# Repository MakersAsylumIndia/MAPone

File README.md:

MAPone
======

a really bare bones Arduino using ATMega 328P DIP, SPI and Serial Interfaces and a few LEDs. Arduino stripped down to bare basics so everyone can afford it.

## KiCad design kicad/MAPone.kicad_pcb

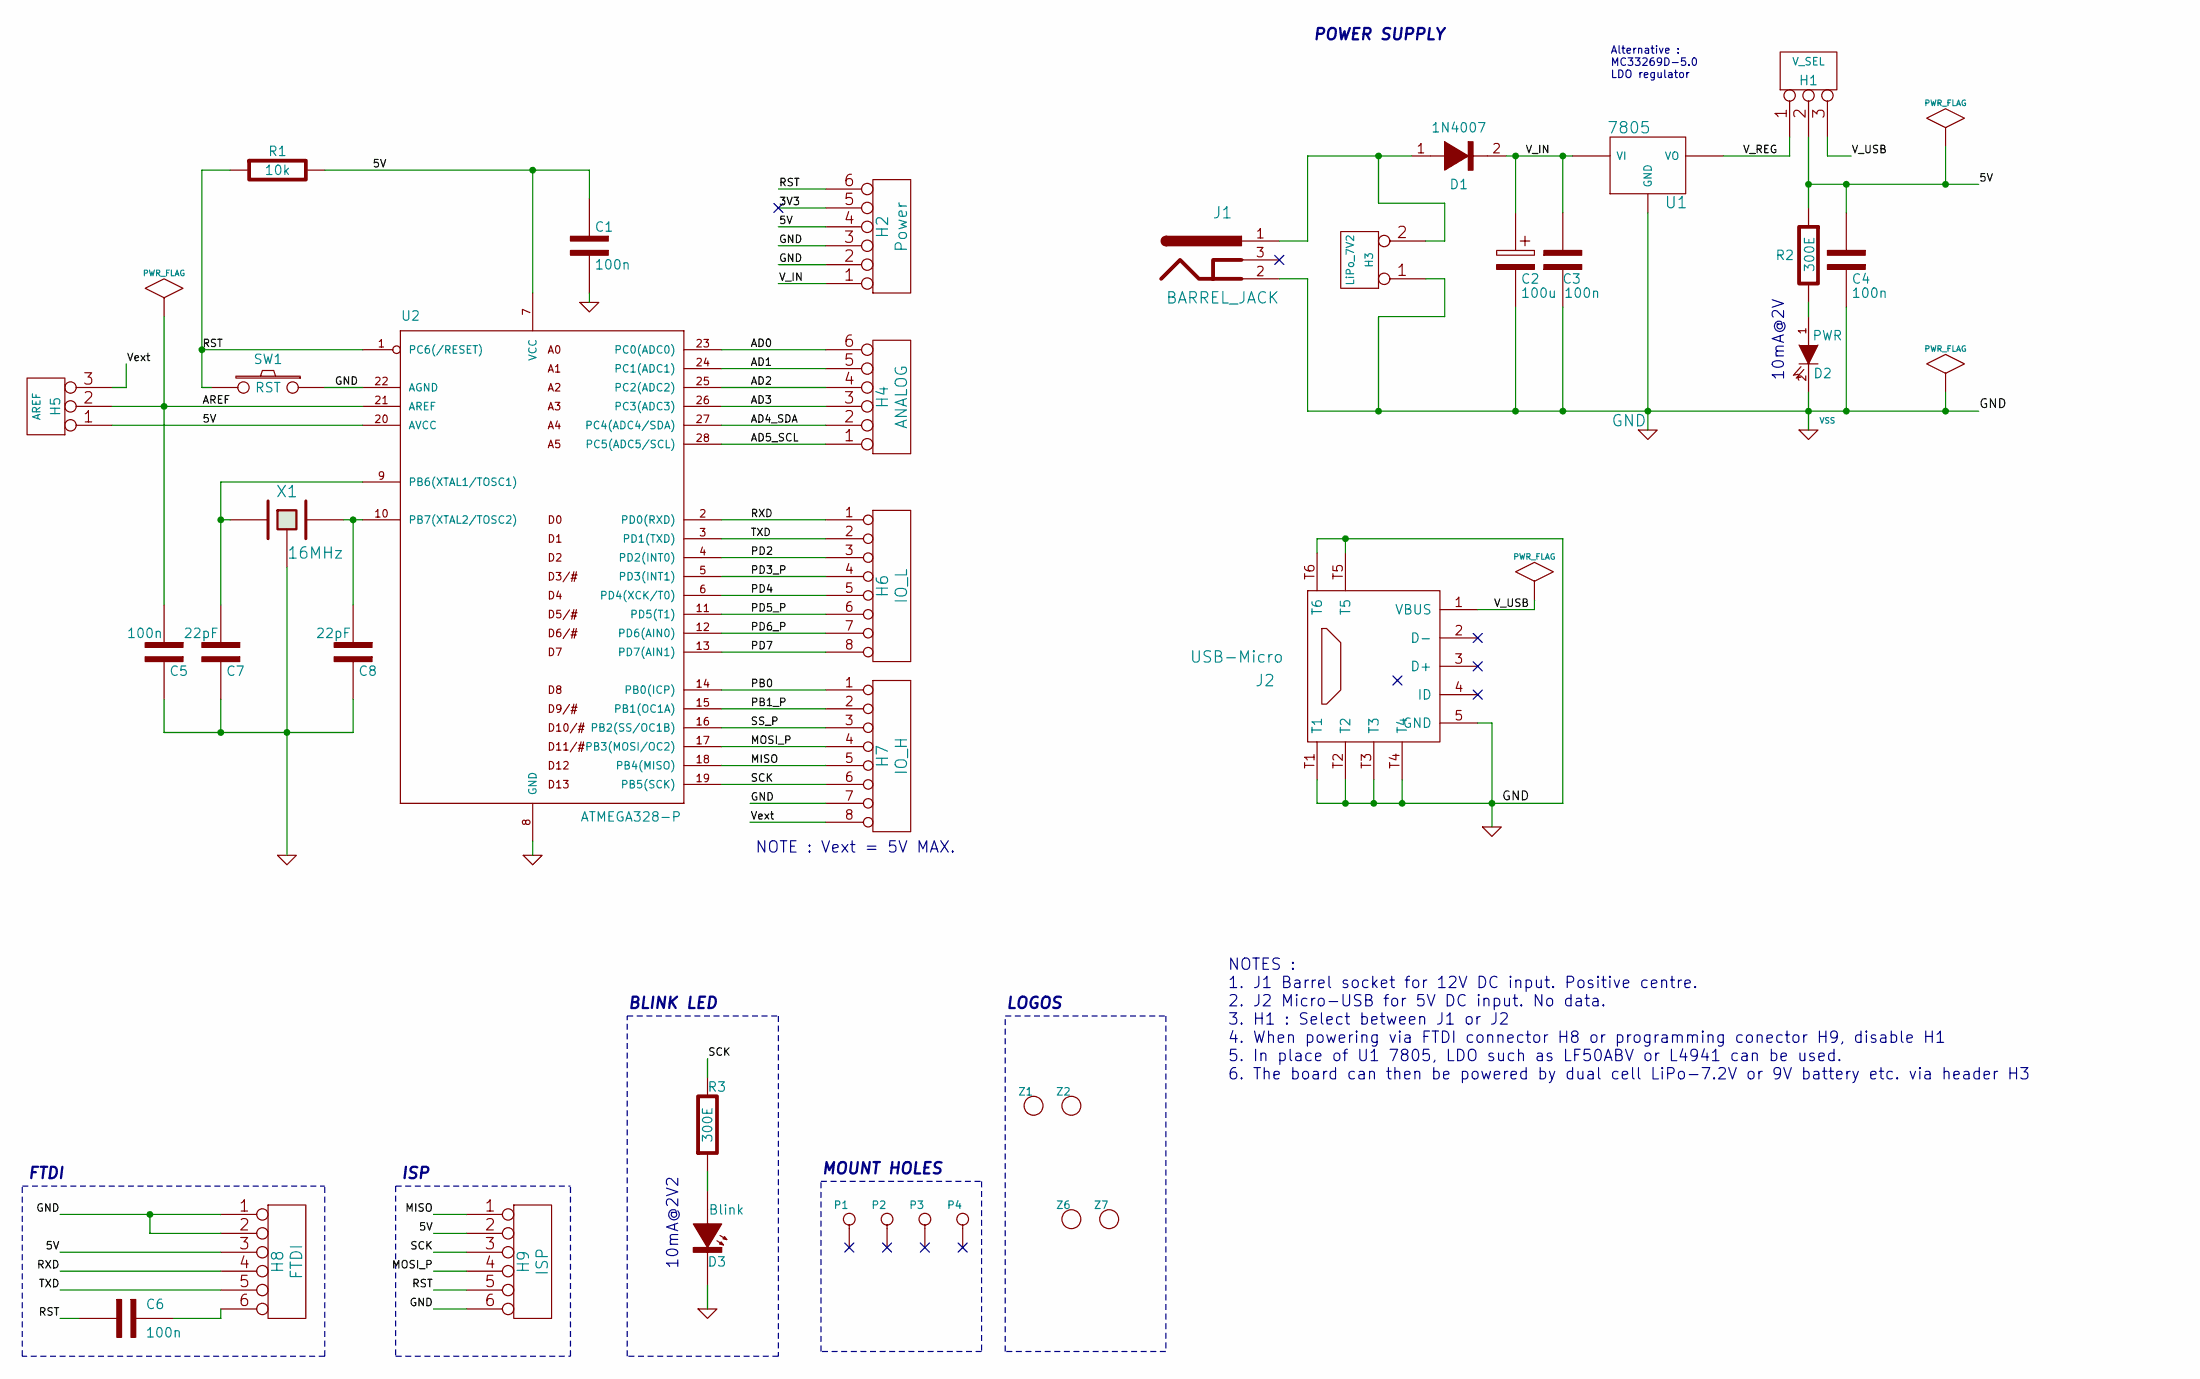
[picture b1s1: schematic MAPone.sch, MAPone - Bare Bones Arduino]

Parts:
C1, C3, C4, C5, C6: 100n; C_0805_HandSoldering
C2: 100u; Elko_vert_11.2x6.3mm_RM2.5
C7, C8: 22pF; C_0805_HandSoldering
D1: 1N4007; Diode_DO-41_SOD81_Vertical_KathodeUp
D2: PWR; LED-3MM
D3: Blink; LED-3MM
H1: V_SEL; Header_3
H2: Power; Socket_Strip_Straight_1x06
H3: LiPo_7V2; Pin_Header_Straight_1x02
H4: ANALOG; Socket_Strip_Straight_1x06
H5: AREF; Header_A_REF
H6: IO_L; Socket_Strip_Straight_1x08
H7: IO_H; Socket_Strip_Straight_1x08
H8: FTDI; Header_FTDI
H9: ISP; Header_ICSP
J1: BARREL_JACK; JACK_ALIM
J2: USB-Micro; USB_B_Micro
P1, P2, P3, P4: CONN_1; vite_3mm
R1: 10k; R_0805_HandSoldering
R2, R3: 300E; R_0805_HandSoldering
SW1: RST; SW-PB; DigiKey P10884S-ND
U1: 7805; LM78XXV
U2: ATMEGA328-P; DIP-28__300_ELL_ZIF
X1: 16MHz; Crystal_HC49-U_Vertical_3Pin; DigiKey 490-1214-ND
Z1, Z2: CONN_1; MA_Logo2
Z6, Z7: CONN_1; OSHW_6mm

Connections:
/5V: C1.1, C4.1, H1.2 (PM), H2.4, H5.1, H8.3, H9.2, R1.1, R2.2, U2.7 (VCC), U2.20 (AVCC)
/AD0: H4.6, U2.23 (PC0(ADC0))
/AD1: H4.5, U2.24 (PC1(ADC1))
/AD2: H4.4, U2.25 (PC2(ADC2))
/AD3: H4.3, U2.26 (PC3(ADC3))
/AD4_SDA: H4.2, U2.27 (PC4(ADC4/SDA))
/AD5_SCL: H4.1, U2.28 (PC5(ADC5/SCL))
/AREF: C5.1, H5.2 (PM), U2.21 (AREF)
/MISO: H7.5, H9.1, U2.18 (PB4(MISO))
/MOSI_P: H7.4, H9.4, U2.17 (PB3(MOSI/OC2))
/PB0: H7.1, U2.14 (PB0(ICP))
/PB1_P: H7.2, U2.15 (PB1(OC1A))
/PD2: H6.3, U2.4 (PD2(INT0))
/PD3_P: H6.4, U2.5 (PD3(INT1))
/PD4: H6.5, U2.6 (PD4(XCK/T0))
/PD5_P: H6.6, U2.11 (PD5(T1))
/PD6_P: H6.7, U2.12 (PD6(AIN0))
/PD7: H6.8, U2.13 (PD7(AIN1))
/RST: C6.1, H2.6, H9.5, R1.2, SW1.2, U2.1 (PC6(/RESET))
/RXD: H6.1, H8.4, U2.2 (PD0(RXD))
/SCK: H7.6, H9.3, R3.1, U2.19 (PB5(SCK))
/SS_P: H7.3, U2.16 (PB2(SS/OC1B))
/TXD: H6.2, H8.5, U2.3 (PD1(TXD))
/V_IN: C2.1, C3.2, D1.2 (Cathode), H2.1, U1.VI
/V_REG: H1.1, U1.VO
/V_USB: H1.3, J2.1 (VBUS)
/Vext: H5.3, H7.8
GND: C1.2, C2.2, C3.1, C4.2, C5.2, C7.2, C8.2, D2.2 (K), D3.2 (Cathode), H2.2, H2.3, H3.1, H7.7, H8.1, H8.2, H9.6, J1.2, J2.5 (GND), J2.T1, J2.T2, J2.T3, J2.T4, J2.T5, J2.T6, SW1.1, U1.GND, U2.8 (GND), U2.22 (AGND), X1.3
unnamed: C6.2, H8.6
unnamed: C7.1, U2.9 (PB6(XTAL1/TOSC1)), X1.1
unnamed: C8.1, U2.10 (PB7(XTAL2/TOSC2)), X1.2
unnamed: D1.1 (Anode), H3.2 (PM), J1.1
unnamed: D2.1 (A), R2.1
unnamed: D3.1 (Anode), R3.2

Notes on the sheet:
Alternative : MC33269D-5.0 LDO regulator
POWER SUPPLY
ISP
FTDI
BLINK LED
MOUNT HOLES
NOTE : Vext = 5V MAX.
NOTES : 1. J1 Barrel socket for 12V DC input. Positive centre. 2. J2 Micro-USB for 5V DC input. No data. 3. H1 : Select between J1 or J2 4. When powering via FTDI connector H8 or programming conector H9, disable H1 5. In place of U1 7805, LDO such as LF50ABV or L4941 can be used. 6. The board can t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
10mA@2V
10mA@2V2
LOGOS

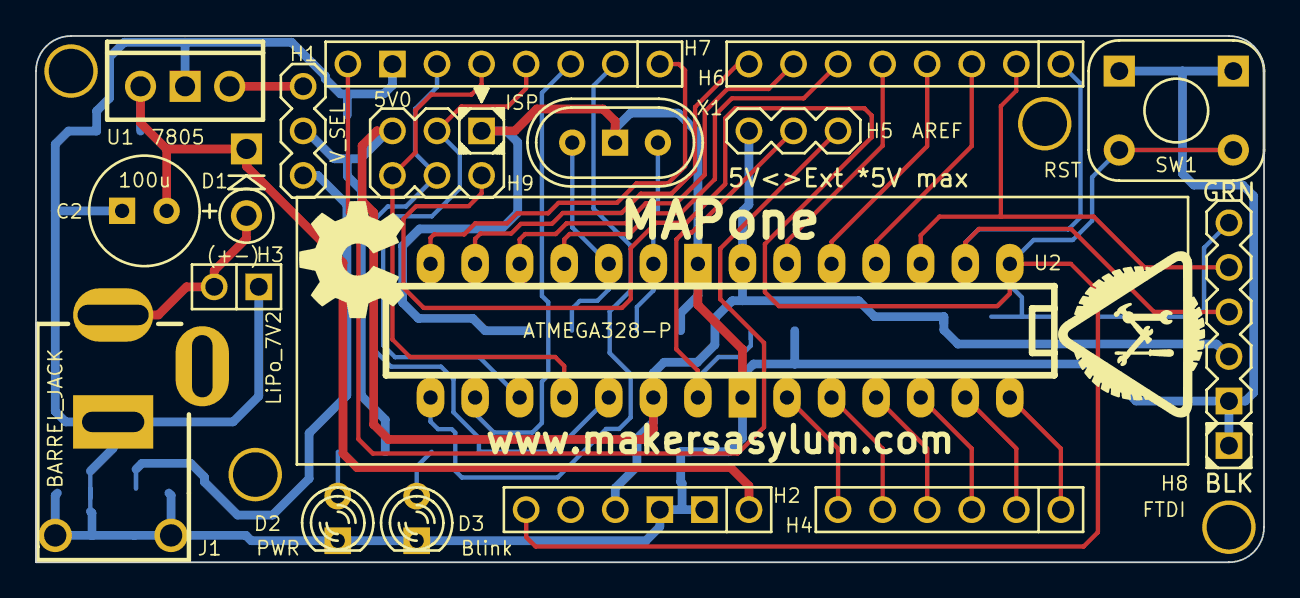
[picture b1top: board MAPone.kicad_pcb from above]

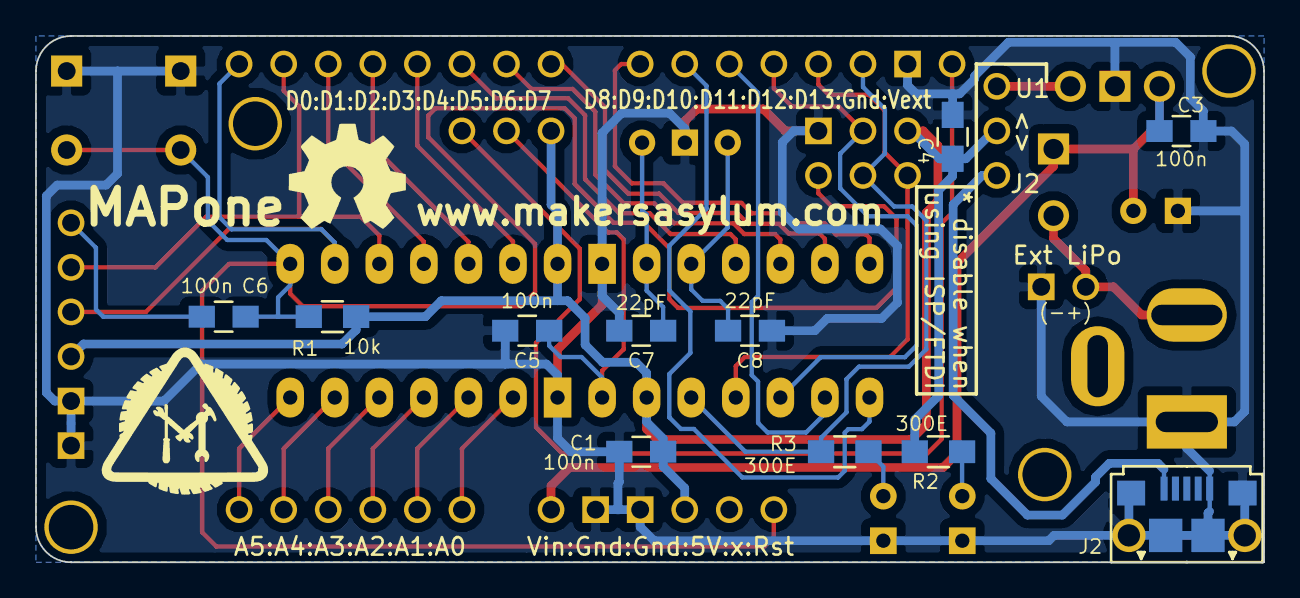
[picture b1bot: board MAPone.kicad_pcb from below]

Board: 2 copper layers, 70.0 x 30.0 mm, 37 parts (13 on the bottom side), 34 nets.

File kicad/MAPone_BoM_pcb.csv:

"Id";"Designator";"Package";"Quantity";"Designation";"Supplier and ref";
1;"U1";"LM78XXV";1;"7805";;;
2;"SW1";"SW-PB";1;"RST";;;
3;"R3,R2";"R_0805_HandSoldering";2;"300E";;;
4;"R1";"R_0805_HandSoldering";1;"10k";;;
5;"P4,P3,P1,P2";"vite_3mm";4;"CONN_1";;;
6;"J1";"JACK_ALIM";1;"BARREL_JACK";;;
7;"H9";"Header_ICSP";1;"ISP";;;
8;"H7";"Socket_Strip_Straight_1x08";1;"IO_H";;;
9;"H6";"Socket_Strip_Straight_1x08";1;"IO_L";;;
10;"H4";"Socket_Strip_Straight_1x06";1;"ANALOG";;;
11;"H2";"Socket_Strip_Straight_1x06";1;"Power";;;
12;"H1";"Header_3";1;"V_SEL";;;
13;"D3";"LED-3MM";1;"Blink";;;
14;"D2";"LED-3MM";1;"PWR";;;
15;"C8,C7";"C_0805_HandSoldering";2;"22pF";;;
16;"C6,C5,C4,C3,C1";"C_0805_HandSoldering";5;"100n";;;
17;"U2";"DIP-28__300_ELL_ZIF";1;"ATMEGA328-P";;;
18;"H8";"Header_FTDI";1;"FTDI";;;
19;"J2";"USB_B_Micro";1;"USB-Micro";;;
20;"X1";"Crystal_HC49-U_Vertical_3Pin";1;"16MHz";;;
21;"D1";"Diode_DO-41_SOD81_Vertical_KathodeUp";1;"1N4007";;;
22;"H5";"Header_A_REF";1;"AREF";;;
23;"Z2,Z1";"MA_Logo2";2;"CONN_1";;;
24;"C2";"Elko_vert_11.2x6.3mm_RM2.5";1;"100u";;;
25;"Z6,Z7";"OSHW_6mm";2;"CONN_1";;;
26;"H3";"Pin_Header_Straight_1x02";1;"LiPo_7V2";;;

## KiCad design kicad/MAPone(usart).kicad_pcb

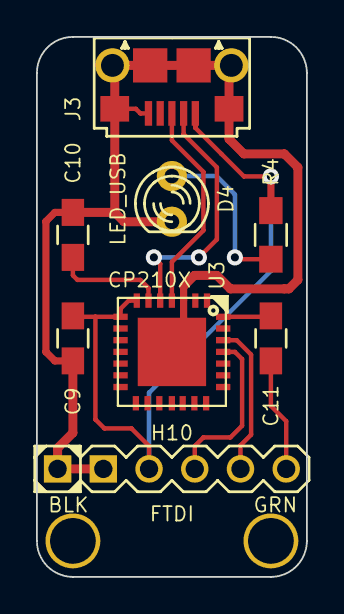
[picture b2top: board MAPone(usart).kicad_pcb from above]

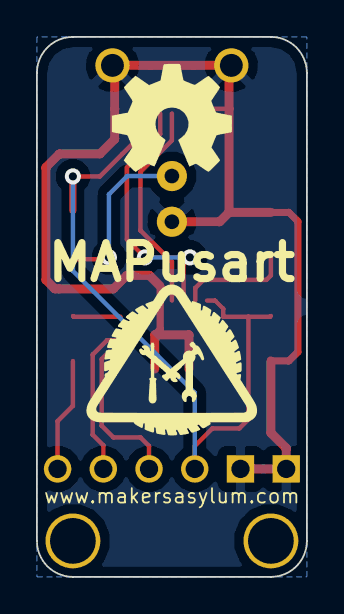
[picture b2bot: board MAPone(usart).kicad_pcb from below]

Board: 2 copper layers, 15.0 x 30.0 mm, 12 parts (2 on the bottom side), 10 nets.

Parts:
C9, C10, C11: 100n; C_0805_HandSoldering
D4: LED_USB; LED-3MM
H10: FTDI; Header_FTDI
J3: USB-Micro; USB_B_Micro
P5, P6: CONN_1; vite_3mm
R4: 300E; R_0805_HandSoldering
U3: CP210X; qfn-28
Z3: CONN_1; MA_Logo2
Z5: CONN_1; OSHW_6mm

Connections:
/USB_UART/3V3: C10.1, U3.6
/USB_UART/5V: C9.1, H10.3, J3.1, R4.1, U3.7, U3.8
/USB_UART/D+: J3.3, U3.4
/USB_UART/D-: J3.2, U3.5
/USB_UART/RST: C11.1, U3.28
/USB_UART/RXD: H10.4, U3.25
/USB_UART/TXD: H10.5, U3.26
GND: C9.2, C10.2, D4.2, H10.1, H10.2, J3.5, J3.T1, J3.T2, J3.T3, J3.T4, J3.T5, J3.T6, U3.3, U3.29
unnamed: C11.2, H10.6
unnamed: D4.1, R4.2

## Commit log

2014-11-17 first commit for MAPone just to set things up
2014-11-17 Added license
2014-11-18 MAPone schematic, work in progress
2014-11-21 Added usb uart sch
2014-11-25 MAPone schematic review + PCB initialized
2014-11-26 MAPone PCB work in progress
2014-11-28 MAPone schematic/pcb complete
2014-11-29 MAPone Schematic, PCB, BoM complete. USB<>UART PCB Pending
2014-11-30 MAPone Schematic, PCB, BoM complete. USB<>UART PCB work in progress
2014-12-01 MAPone USB<>USART complete. preliminary gerbers generated
2014-12-01 MAPone changed header locations to fit Breadboard instead of Arduino
2014-12-01 MAPone realigned headers to fit 0.1 breadboard
2014-12-02 finalized schematic design
2014-12-02 MAPone made MAPusart smaller
2014-12-02 MAPone hived off USB<>UART bridge to separate project MAPusart
2014-12-03 MAPone complete and ready for prototyping
2014-12-04 MAPone & MAPusart made a common gerbe
2014-12-09 MAPone updated BoM for visha
2015-02-05 BoM update, added assemby instructions
2015-02-19 added a few images
